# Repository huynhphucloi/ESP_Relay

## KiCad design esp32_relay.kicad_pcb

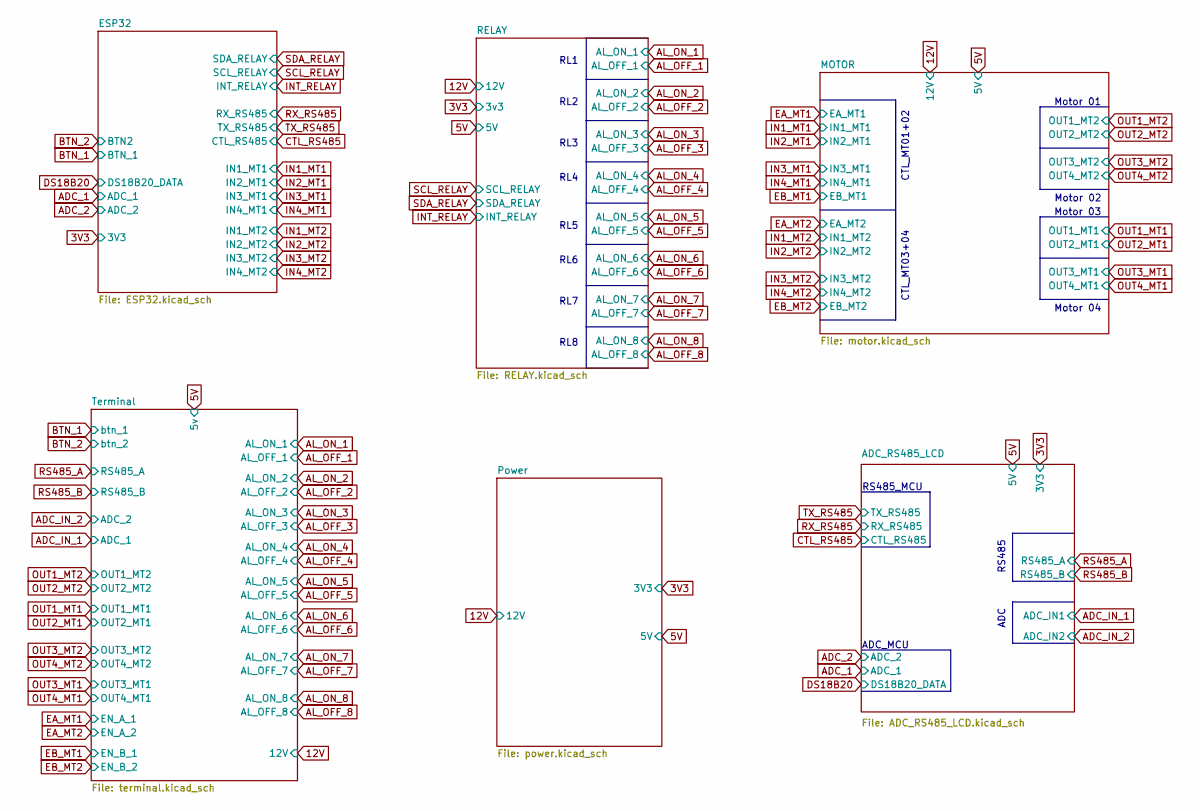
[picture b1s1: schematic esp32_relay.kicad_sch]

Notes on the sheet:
RL1
RL6
RL8
Motor 01
RS485
RL5
Motor 04
RL2
CTL_MT01+02
Motor 03
RL3
RL7
ADC
RS485_MCU
RL4
Motor 02
ADC_MCU
CTL_MT03+04

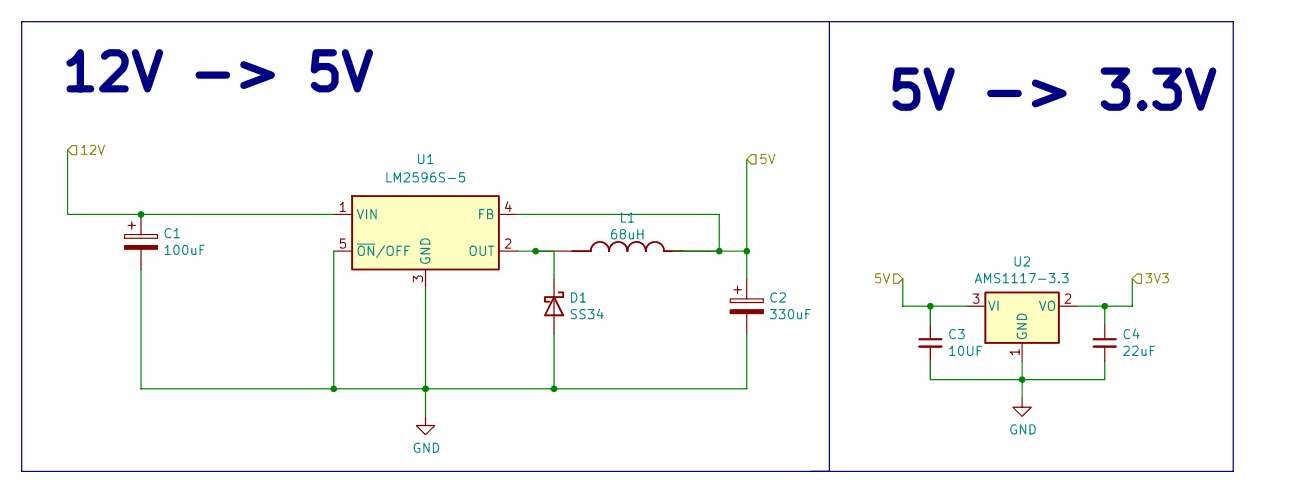
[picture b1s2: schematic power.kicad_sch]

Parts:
C1: 100uF; CP_Radial_D6.3mm_P2.50mm
C2: 330uF; CP_Radial_D6.3mm_P2.50mm
C3: 10UF; C_Disc_D3.0mm_W2.0mm_P2.50mm
C4: 22uF; C_Disc_D3.0mm_W2.0mm_P2.50mm
D1: SS34; D_DO-41_SOD81_P7.62mm_Horizontal
L1: 68uH; L_Radial_D6.0mm_P4.00mm
U1: LM2596S-5; TO-263-5_TabPin3
U2: AMS1117-3.3; SOT-223-3_TabPin2

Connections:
3V3: C4.1, U2.2 (VO); also elsewhere on the board
5V: C2.1, C3.1, L1.2, U1.4 (FB), U2.3 (VI); also elsewhere on the board
12V: C1.1, U1.1 (VIN); also elsewhere on the board
GND: C1.2, C2.2, C3.2, C4.2, D1.2 (A), U1.3 (GND), U1.5 (~ON/OFF), U2.1 (GND); also elsewhere on the board
unnamed: D1.1 (K), L1.1, U1.2 (OUT)

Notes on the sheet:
12V -> 5V
5V -> 3.3V

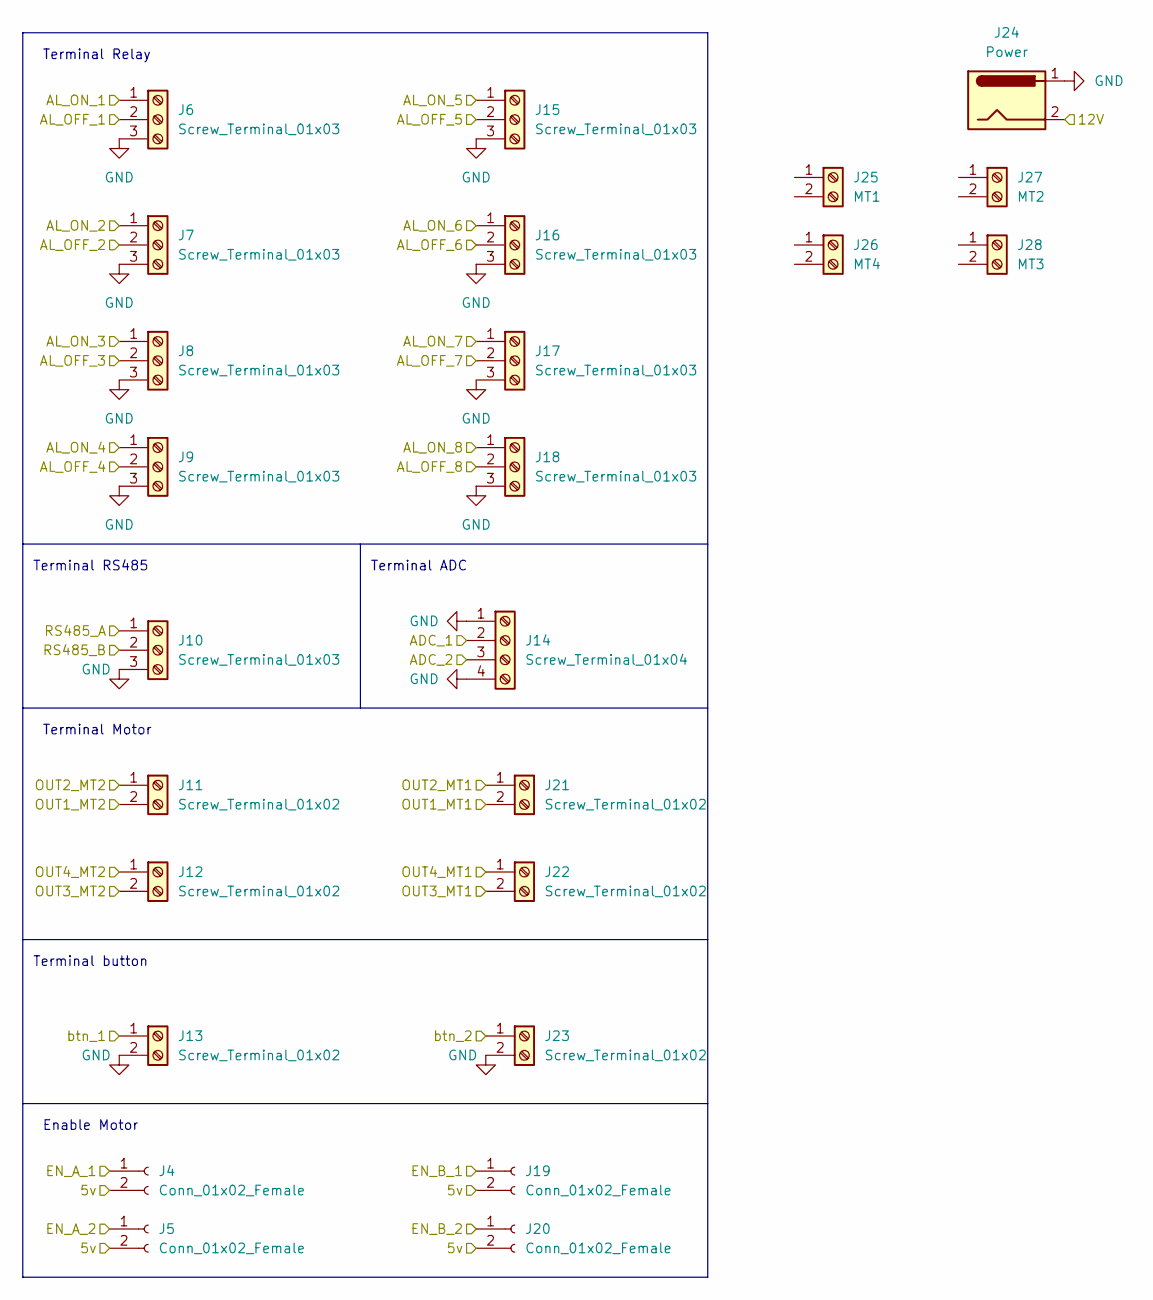
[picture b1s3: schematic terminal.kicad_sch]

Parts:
J4, J5, J19, J20: Conn_01x02_Female; PinHeader_1x02_P2.54mm_Vertical
J6, J7, J8, J9, J10, J15, J16, J17, J18: Screw_Terminal_01x03; TerminalBlock_Phoenix_MKDS-1,5-3_1x03_P5.00mm_Horizontal
J11, J12, J13, J21, J22, J23: Screw_Terminal_01x02; TerminalBlock_Phoenix_MKDS-1,5-2_1x02_P5.00mm_Horizontal
J14: Screw_Terminal_01x04; TerminalBlock_Phoenix_MKDS-1,5-4_1x04_P5.00mm_Horizontal
J24: Power; TerminalBlock_Phoenix_MKDS-1,5-2_1x02_P5.00mm_Horizontal
J25: MT1; TerminalBlock_Phoenix_MKDS-1,5-2_1x02_P5.00mm_Horizontal
J26: MT4; TerminalBlock_Phoenix_MKDS-1,5-2_1x02_P5.00mm_Horizontal
J27: MT2; TerminalBlock_Phoenix_MKDS-1,5-2_1x02_P5.00mm_Horizontal
J28: MT3; TerminalBlock_Phoenix_MKDS-1,5-2_1x02_P5.00mm_Horizontal

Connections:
5V: J4.2, J5.2, J19.2, J20.2; also elsewhere on the board
12V: J24.2; also elsewhere on the board
ADC_IN_1: J14.2; also elsewhere on the board
ADC_IN_2: J14.3; also elsewhere on the board
AL_OFF_1: J6.2; also elsewhere on the board
AL_OFF_2: J7.2; also elsewhere on the board
AL_OFF_3: J8.2; also elsewhere on the board
AL_OFF_4: J9.2; also elsewhere on the board
AL_OFF_5: J15.2; also elsewhere on the board
AL_OFF_6: J16.2; also elsewhere on the board
AL_OFF_7: J17.2; also elsewhere on the board
AL_OFF_8: J18.2; also elsewhere on the board
AL_ON_1: J6.1; also elsewhere on the board
AL_ON_2: J7.1; also elsewhere on the board
AL_ON_3: J8.1; also elsewhere on the board
AL_ON_4: J9.1; also elsewhere on the board
AL_ON_5: J15.1; also elsewhere on the board
AL_ON_6: J16.1; also elsewhere on the board
AL_ON_7: J17.1; also elsewhere on the board
AL_ON_8: J18.1; also elsewhere on the board
BTN_1: J13.1; also elsewhere on the board
BTN_2: J23.1; also elsewhere on the board
EA_MT1: J4.1; also elsewhere on the board
EA_MT2: J5.1; also elsewhere on the board
EB_MT1: J19.1; also elsewhere on the board
EB_MT2: J20.1; also elsewhere on the board
GND: J6.3, J7.3, J8.3, J9.3, J10.3, J13.2, J14.1, J14.4, J15.3, J16.3, J17.3, J18.3, J23.2, J24.1; also elsewhere on the board
OUT1_MT1: J21.2; also elsewhere on the board
OUT1_MT2: J11.2; also elsewhere on the board
OUT2_MT1: J21.1; also elsewhere on the board
OUT2_MT2: J11.1; also elsewhere on the board
OUT3_MT1: J22.2; also elsewhere on the board
OUT3_MT2: J12.2; also elsewhere on the board
OUT4_MT1: J22.1; also elsewhere on the board
OUT4_MT2: J12.1; also elsewhere on the board
RS485_A: J10.1; also elsewhere on the board
RS485_B: J10.2; also elsewhere on the board

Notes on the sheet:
Terminal Relay
Terminal button
Enable Motor
Terminal RS485
Terminal ADC
Terminal Motor

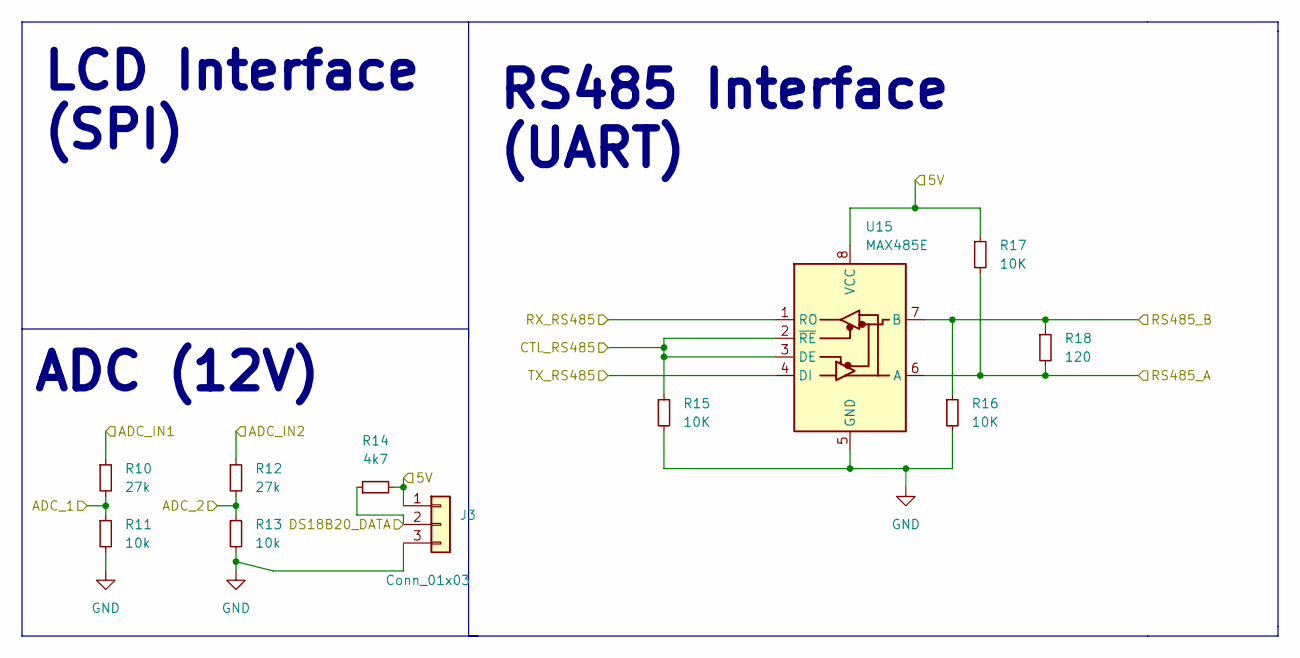
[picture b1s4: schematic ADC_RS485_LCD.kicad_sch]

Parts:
J3: Conn_01x03; TerminalBlock_Phoenix_MKDS-1,5-3_1x03_P5.00mm_Horizontal
R10, R12: 27k; R_Axial_DIN0204_L3.6mm_D1.6mm_P5.08mm_Horizontal
R11, R13: 10k; R_Axial_DIN0204_L3.6mm_D1.6mm_P5.08mm_Horizontal
R14: 4k7; R_Axial_DIN0204_L3.6mm_D1.6mm_P5.08mm_Horizontal
R15, R16, R17: 10K; R_Axial_DIN0204_L3.6mm_D1.6mm_P5.08mm_Horizontal
R18: 120; R_Axial_DIN0204_L3.6mm_D1.6mm_P5.08mm_Horizontal
U15: MAX485E; DIP-8_W7.62mm_LongPads

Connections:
5V: J3.1, R14.2, R17.1, U15.8 (VCC); also elsewhere on the board
ADC_1: R10.2, R11.1; also elsewhere on the board
ADC_2: R12.2, R13.1; also elsewhere on the board
ADC_IN_1: R10.1; also elsewhere on the board
ADC_IN_2: R12.1; also elsewhere on the board
CTL_RS485: R15.1, U15.2 (~RE), U15.3 (DE); also elsewhere on the board
DS18B20: J3.2, R14.1; also elsewhere on the board
GND: J3.3, R11.2, R13.2, R15.2, R16.2, U15.5 (GND); also elsewhere on the board
RS485_A: R17.2, R18.2, U15.6 (A); also elsewhere on the board
RS485_B: R16.1, R18.1, U15.7 (B); also elsewhere on the board
RX_RS485: U15.1 (RO); also elsewhere on the board
TX_RS485: U15.4 (DI); also elsewhere on the board

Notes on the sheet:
ADC (12V)
LCD Interface (SPI)
RS485 Interface (UART)

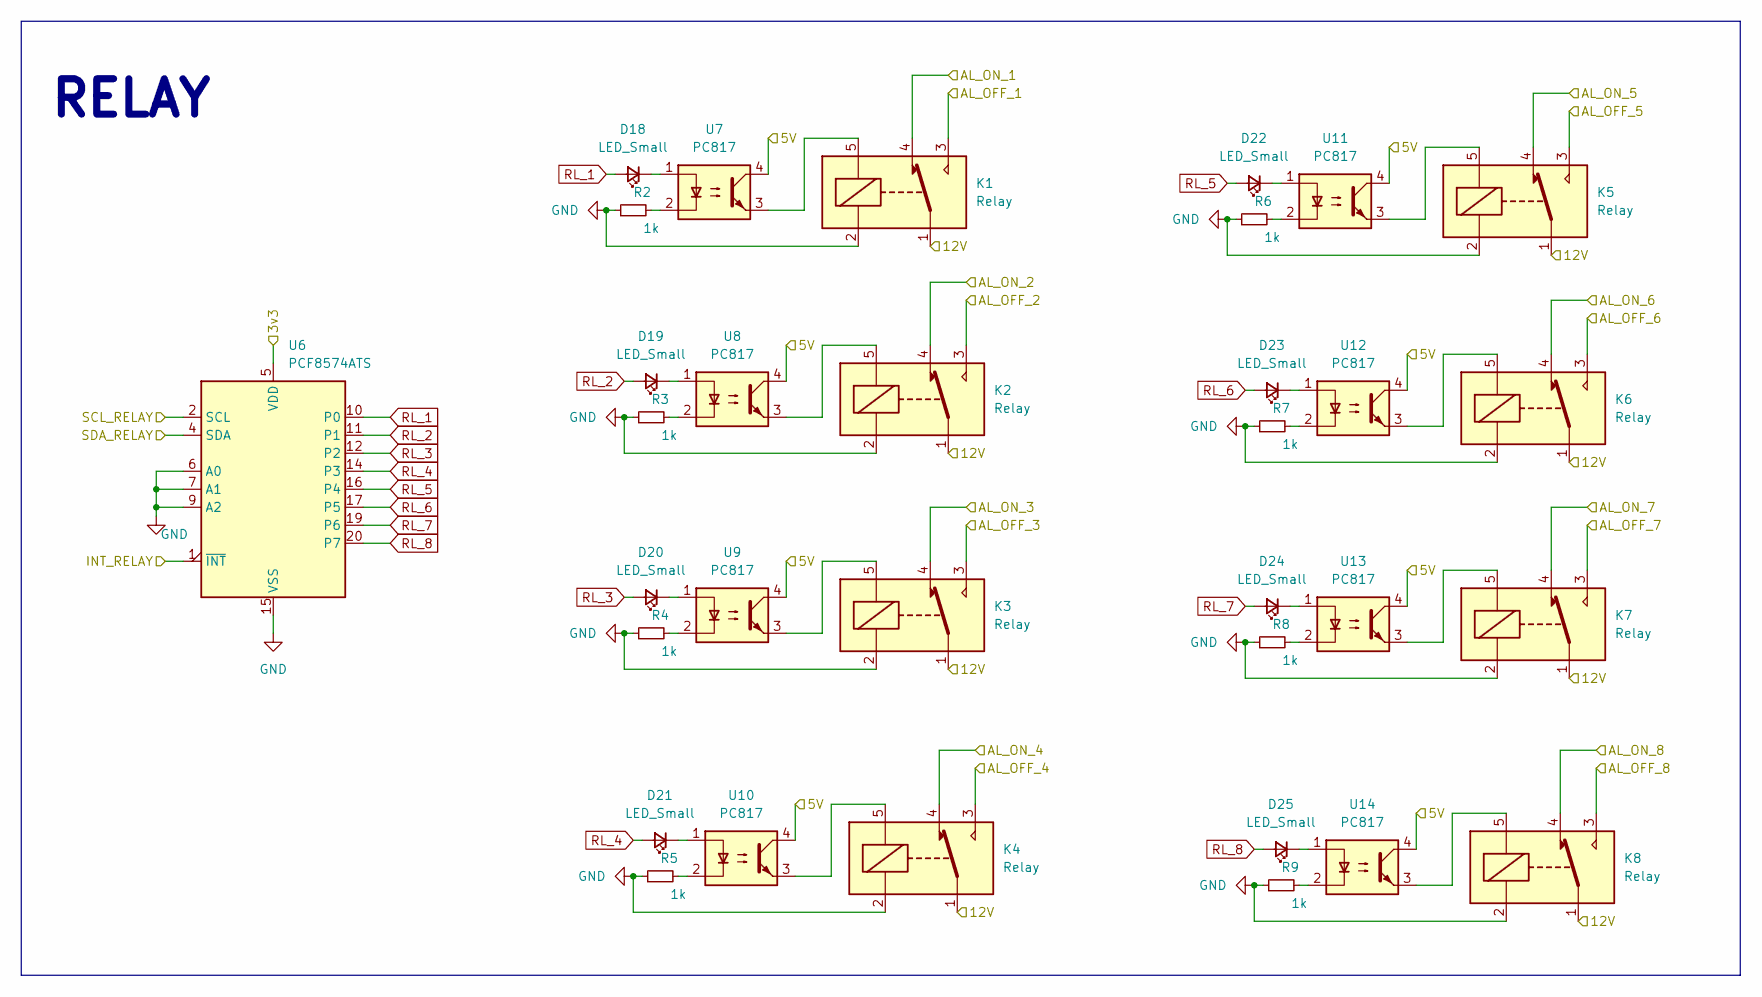
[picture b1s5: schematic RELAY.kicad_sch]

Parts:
D18, D19, D20, D21, D22, D23, D24, D25: LED_Small; LED_D1.8mm_W3.3mm_H2.4mm
K1, K2, K3, K4, K5, K6, K7, K8: Relay; Relay_SPDT_SANYOU_SRD_Series_Form_C
R2, R3, R4, R5, R6, R7, R8, R9: 1k; R_Axial_DIN0204_L3.6mm_D1.6mm_P5.08mm_Horizontal
U6: PCF8574ATS; SSOP-20_4.4x6.5mm_P0.65mm
U7, U8, U9, U10, U11, U12, U13, U14: PC817; DIP-4_W7.62mm

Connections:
3V3: U6.5 (VDD); also elsewhere on the board
5V: U7.4, U8.4, U9.4, U10.4, U11.4, U12.4, U13.4, U14.4; also elsewhere on the board
12V: K1.1, K2.1, K3.1, K4.1, K5.1, K6.1, K7.1, K8.1; also elsewhere on the board
AL_OFF_1: K1.3; also elsewhere on the board
AL_OFF_2: K2.3; also elsewhere on the board
AL_OFF_3: K3.3; also elsewhere on the board
AL_OFF_4: K4.3; also elsewhere on the board
AL_OFF_5: K5.3; also elsewhere on the board
AL_OFF_6: K6.3; also elsewhere on the board
AL_OFF_7: K7.3; also elsewhere on the board
AL_OFF_8: K8.3; also elsewhere on the board
AL_ON_1: K1.4; also elsewhere on the board
AL_ON_2: K2.4; also elsewhere on the board
AL_ON_3: K3.4; also elsewhere on the board
AL_ON_4: K4.4; also elsewhere on the board
AL_ON_5: K5.4; also elsewhere on the board
AL_ON_6: K6.4; also elsewhere on the board
AL_ON_7: K7.4; also elsewhere on the board
AL_ON_8: K8.4; also elsewhere on the board
GND: K1.2, K2.2, K3.2, K4.2, K5.2, K6.2, K7.2, K8.2, R2.1, R3.1, R4.1, R5.1, R6.1, R7.1, R8.1, R9.1, U6.6 (A0), U6.7 (A1), U6.9 (A2), U6.15 (VSS); also elsewhere on the board
INT_RELAY: U6.1 (~INT); also elsewhere on the board
unnamed: D18.1 (K), U7.1
unnamed: D19.1 (K), U8.1
unnamed: D20.1 (K), U9.1
unnamed: D21.1 (K), U10.1
unnamed: D22.1 (K), U11.1
unnamed: D23.1 (K), U12.1
unnamed: D24.1 (K), U13.1
unnamed: D25.1 (K), U14.1
unnamed: K1.5, U7.3
unnamed: K2.5, U8.3
unnamed: K3.5, U9.3
unnamed: K4.5, U10.3
unnamed: K5.5, U11.3
unnamed: K6.5, U12.3
unnamed: K7.5, U13.3
unnamed: K8.5, U14.3
unnamed: R2.2, U7.2
unnamed: R3.2, U8.2
unnamed: R4.2, U9.2
unnamed: R5.2, U10.2
unnamed: R6.2, U11.2
unnamed: R7.2, U12.2
unnamed: R8.2, U13.2
unnamed: R9.2, U14.2
RL_1: D18.2 (A), U6.10 (P0)
RL_2: D19.2 (A), U6.11 (P1)
RL_3: D20.2 (A), U6.12 (P2)
RL_4: D21.2 (A), U6.14 (P3)
RL_5: D22.2 (A), U6.16 (P4)
RL_6: D23.2 (A), U6.17 (P5)
RL_7: D24.2 (A), U6.19 (P6)
RL_8: D25.2 (A), U6.20 (P7)
SCL_RELAY: U6.2 (SCL); also elsewhere on the board
SDA_RELAY: U6.4 (SDA); also elsewhere on the board

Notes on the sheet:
RELAY

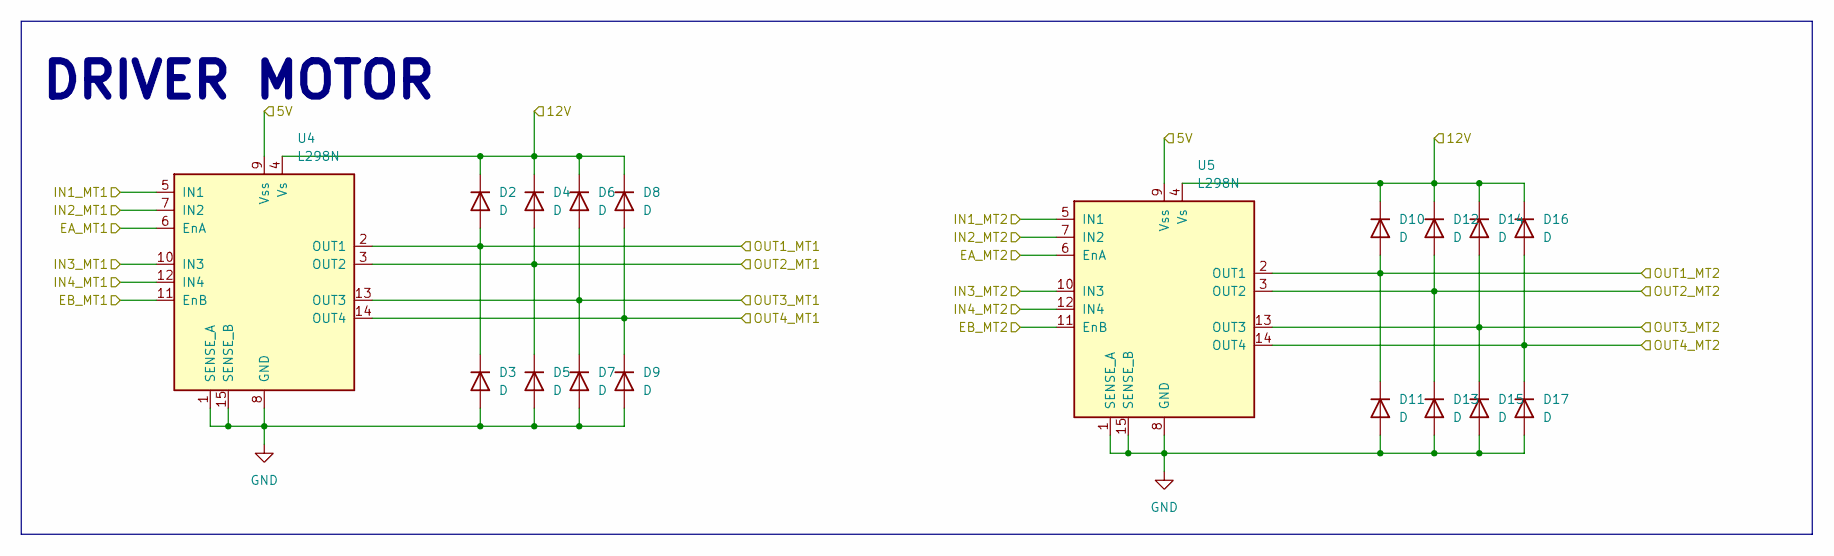
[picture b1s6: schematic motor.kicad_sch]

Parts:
D2, D3, D4, D5, D6, D7, D8, D9, D10, D11, D12, D13, D14, D15, D16, D17: D; D_DO-41_SOD81_P7.62mm_Horizontal
U4, U5: L298N; TO-220-15_P2.54x2.54mm_StaggerOdd_Lead4.58mm_Vertical

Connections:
5V: U4.9 (Vss), U5.9 (Vss); also elsewhere on the board
12V: D2.1 (K), D4.1 (K), D6.1 (K), D8.1 (K), D10.1 (K), D12.1 (K), D14.1 (K), D16.1 (K), U4.4 (Vs), U5.4 (Vs); also elsewhere on the board
EA_MT1: U4.6 (EnA); also elsewhere on the board
EA_MT2: U5.6 (EnA); also elsewhere on the board
EB_MT1: U4.11 (EnB); also elsewhere on the board
EB_MT2: U5.11 (EnB); also elsewhere on the board
GND: D3.2 (A), D5.2 (A), D7.2 (A), D9.2 (A), D11.2 (A), D13.2 (A), D15.2 (A), D17.2 (A), U4.1 (SENSE_A), U4.8 (GND), U4.15 (SENSE_B), U5.1 (SENSE_A), U5.8 (GND), U5.15 (SENSE_B); also elsewhere on the board
IN1_MT1: U4.5 (IN1); also elsewhere on the board
IN1_MT2: U5.5 (IN1); also elsewhere on the board
IN2_MT1: U4.7 (IN2); also elsewhere on the board
IN2_MT2: U5.7 (IN2); also elsewhere on the board
IN3_MT1: U4.10 (IN3); also elsewhere on the board
IN3_MT2: U5.10 (IN3); also elsewhere on the board
IN4_MT1: U4.12 (IN4); also elsewhere on the board
IN4_MT2: U5.12 (IN4); also elsewhere on the board
OUT1_MT1: D2.2 (A), D3.1 (K), U4.2 (OUT1); also elsewhere on the board
OUT1_MT2: D10.2 (A), D11.1 (K), U5.2 (OUT1); also elsewhere on the board
OUT2_MT1: D4.2 (A), D5.1 (K), U4.3 (OUT2); also elsewhere on the board
OUT2_MT2: D12.2 (A), D13.1 (K), U5.3 (OUT2); also elsewhere on the board
OUT3_MT1: D6.2 (A), D7.1 (K), U4.13 (OUT3); also elsewhere on the board
OUT3_MT2: D14.2 (A), D15.1 (K), U5.13 (OUT3); also elsewhere on the board
OUT4_MT1: D8.2 (A), D9.1 (K), U4.14 (OUT4); also elsewhere on the board
OUT4_MT2: D16.2 (A), D17.1 (K), U5.14 (OUT4); also elsewhere on the board

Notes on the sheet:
DRIVER MOTOR

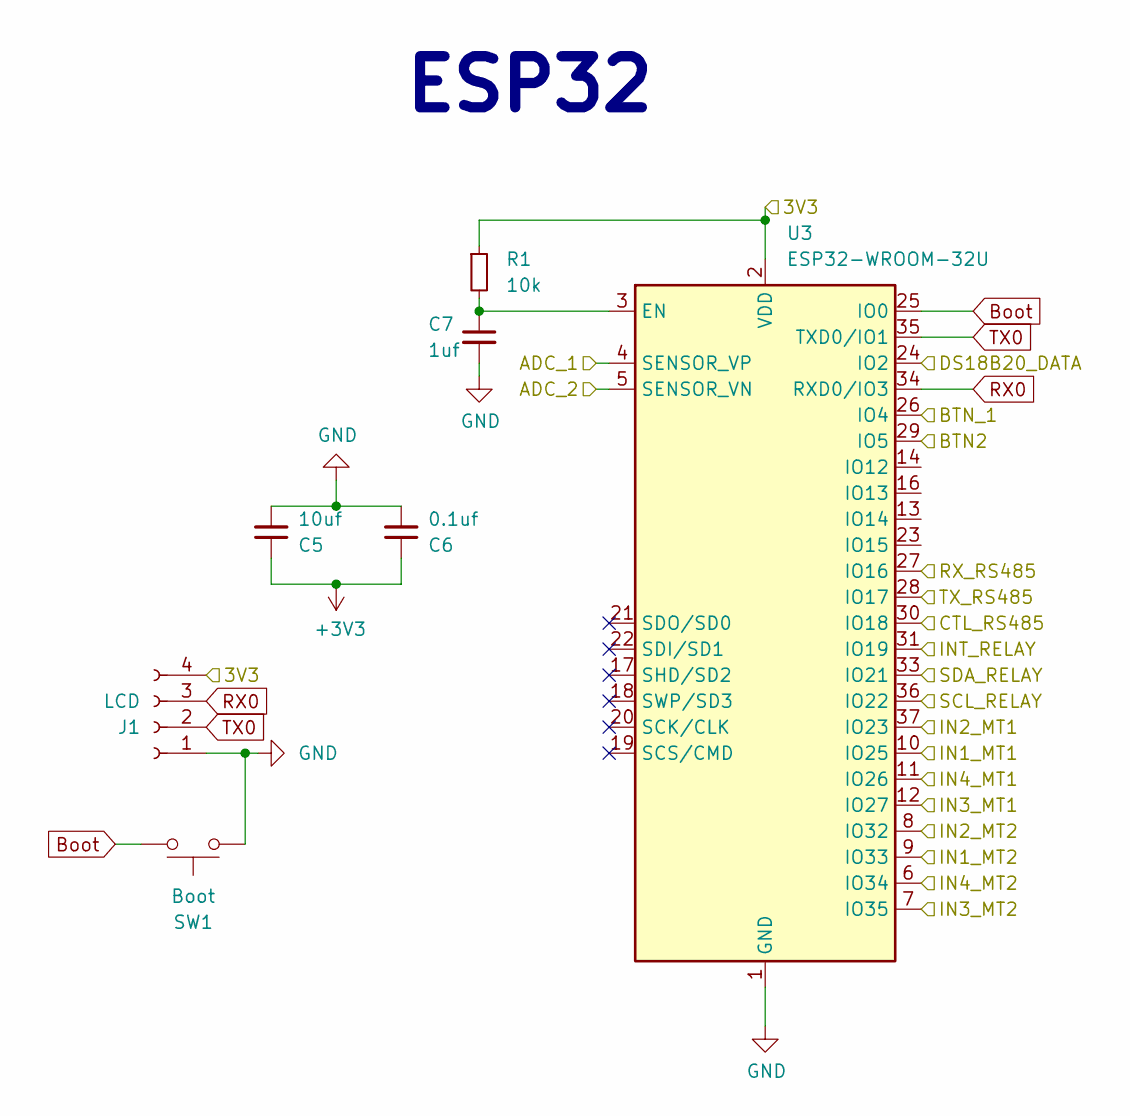
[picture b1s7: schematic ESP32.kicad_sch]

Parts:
C5: 10uf; C_Disc_D3.0mm_W2.0mm_P2.50mm
C6: 0.1uf; C_Disc_D3.0mm_W2.0mm_P2.50mm
C7: 1uf; C_Disc_D3.0mm_W2.0mm_P2.50mm
J1: LCD; PinHeader_1x04_P2.54mm_Vertical
R1: 10k; R_Axial_DIN0204_L3.6mm_D1.6mm_P5.08mm_Horizontal
SW1: Boot; SW_PUSH_6mm_H4.3mm
U3: ESP32-WROOM-32U

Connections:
3V3: J1.4, R1.1, U3.2 (VDD); also elsewhere on the board
+3V3: C5.1, C6.1
ADC_1: U3.4 (SENSOR_VP); also elsewhere on the board
ADC_2: U3.5 (SENSOR_VN); also elsewhere on the board
BTN_1: U3.26 (IO4); also elsewhere on the board
BTN_2: U3.29 (IO5); also elsewhere on the board
Boot: SW1.1, U3.25 (IO0)
CTL_RS485: U3.30 (IO18); also elsewhere on the board
DS18B20: U3.24 (IO2); also elsewhere on the board
GND: C5.2, C6.2, C7.2, J1.1, SW1.2, U3.1 (GND), U3.15 (GND), U3.38 (GND), U3.39 (GND); also elsewhere on the board
IN1_MT1: U3.10 (IO25); also elsewhere on the board
IN1_MT2: U3.9 (IO33); also elsewhere on the board
IN2_MT1: U3.37 (IO23); also elsewhere on the board
IN2_MT2: U3.8 (IO32); also elsewhere on the board
IN3_MT1: U3.12 (IO27); also elsewhere on the board
IN3_MT2: U3.7 (IO35); also elsewhere on the board
IN4_MT1: U3.11 (IO26); also elsewhere on the board
IN4_MT2: U3.6 (IO34); also elsewhere on the board
INT_RELAY: U3.31 (IO19); also elsewhere on the board
unnamed: C7.1, R1.2, U3.3 (EN)
RX0: J1.3, U3.34 (RXD0/IO3)
RX_RS485: U3.27 (IO16); also elsewhere on the board
SCL_RELAY: U3.36 (IO22); also elsewhere on the board
SDA_RELAY: U3.33 (IO21); also elsewhere on the board
TX0: J1.2, U3.35 (TXD0/IO1)
TX_RS485: U3.28 (IO17); also elsewhere on the board

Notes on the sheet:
ESP32

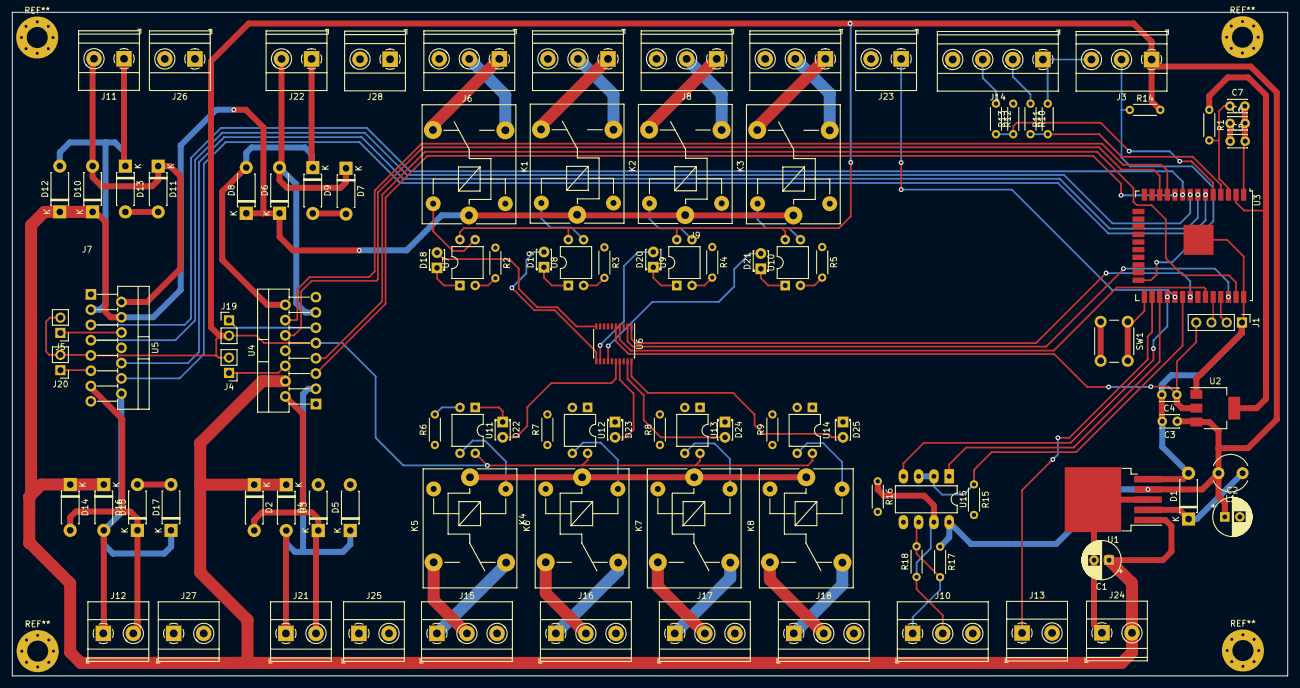
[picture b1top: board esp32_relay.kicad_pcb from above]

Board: 2 copper layers, 212.1 x 110.4 mm, 102 parts (0 on the bottom side), 93 nets.

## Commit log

2022-10-15 Init Project
2022-10-15 fix position
